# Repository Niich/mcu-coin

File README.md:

# mcu-coin
## Design Goals
- make a device that is similare in form factor to military challange coins
- production cost needs to be in the range of traditional coins ($5-$15)

## V1.0 features
- based on ESP32C3
- 100mAh 302020 battery
- 7 addressable RGBs
- 2 GPIO buttons
- hardware power on/off and boot select **
    - to reduce power draw when off and to guard against bad firmare bricking the device since once it is assembled, battery soldered in and parts glued together, removing power to reset device would be very difficult.
- USB charging
- wireless charging ***
- WiFi ***
- bluetooth ***

** not working on original design but manual fix found

*** Currently not working

## v1.0 known issues
- ✅ SW2 boot select button/GPIO9 
    - **Expected:** when held during boot ESP enters flashing mode.
    - **Observed:** device does not enter boot mode when button is held during boot.
    - **Fix:** After reviewing the ESP docs and the schematic issue was found to be that the button was connected to 3.3v instead of ground. Fixed by cutting trace to +3.3 and bridging the pin to the ground plane.

- ✅ SW1 on-off/GPIO6 
    - **Expected:** when device is off pressing this button should turn on the device. while device is active quick presses should be detected on GPIO6. Long pressing when "on" should turn off the device. 
    - **Observed:** Button does not turn the device on. but once on the press can be detected on GPIO6 and long press does turn the device off.
    - **Fix:** After reviewing the schematic issue was found to be that the button was connected to "MainPower" instead of +BATT. meaning that when the device is off there is no voltage on the switch so pressing it did nothing. Fix is connecting the button to +BATT and cutting trace to "MainPower"
    
- ❌ Wireless charging
    - **Expected:** when device placed on wireless charging pad it charges
    - **Observed:** Pad detects device but power delivery never stabalises it seems to be failing the negotiation. Issue has been observed on two differant wireless power transmitters
    - **Fix:** NONE. This is due to poor efficiency. If placed just right, wireless charging will work, but devices get VERY hot. To resolve this, the coil needs to be measured and revised in future designs. Additionally, the QI standard specifies a ferite layer behind the coil, which is not possible with the current placement of the coil.
- ❌ 2.4Ghz wireless (WifI/bluetooth)
    - **Expected:** device connects to WiFi.
    - **Observed:** When 2.4Ghz functions are enabled in firmware the device crashes. 
    - **Fix:** NONE. This is related to the luckup/crashing. When WiFi is activated, it interferes with the main clock and causes the device to lockup/crash.
- ❌ Crashing and hard locks
    - **Expected:** Device runs coninualy until turned of or battery is drained.
    - **Observed:** The device runs for a while but randomly locks up and requires a restart. The issue seems worse when LEDs are at full power.
    - **Fix:** NONE: This is caused by bad placement and routing of the main clock signal. Due to poor design, there is interferance and cross-talk that degrade the clock signal and cause CPU lockup.
- [ ] Acrylic spacer and diffuser
    - **Expected:** Top and bottom PCB are seperated and atteched to a 3mm acrylic spacer.
    - **Observed:** Although the 302020 battery is listed as 3mm thick it is actualy slightly larger so the acrylic part is not thick enought to connect both sides without bending and placing pressure on the LiPo battery
    - **Ideas:** Make a thicker spacer. 1/8" might be ehough since that is 3.17mm

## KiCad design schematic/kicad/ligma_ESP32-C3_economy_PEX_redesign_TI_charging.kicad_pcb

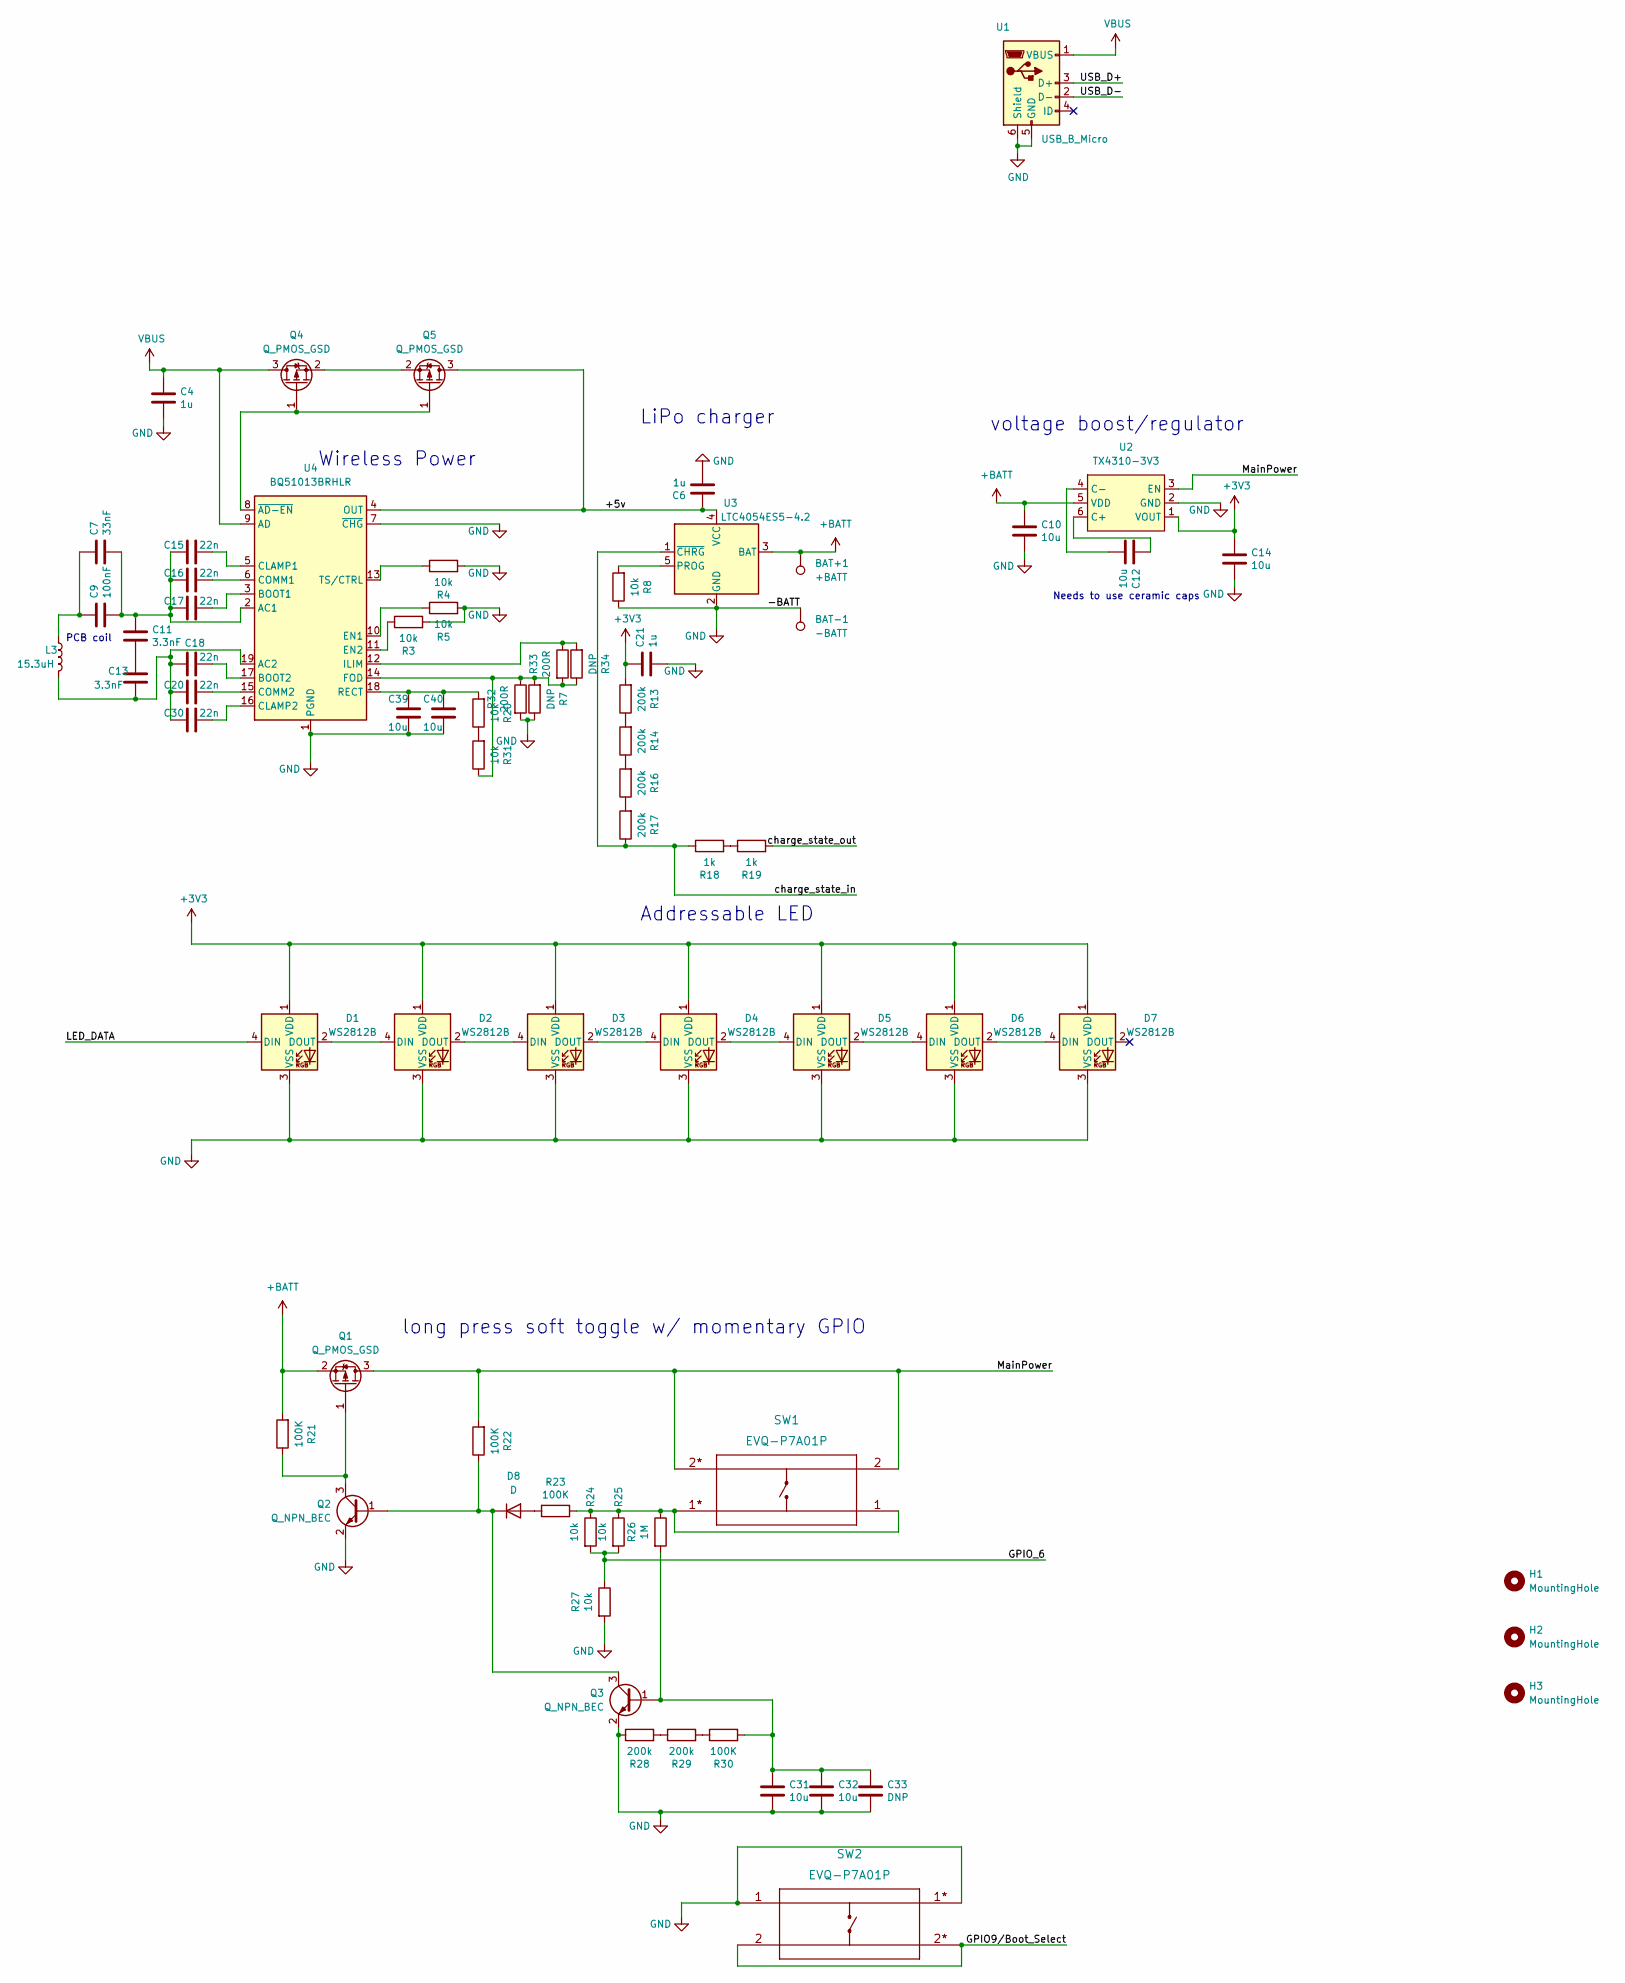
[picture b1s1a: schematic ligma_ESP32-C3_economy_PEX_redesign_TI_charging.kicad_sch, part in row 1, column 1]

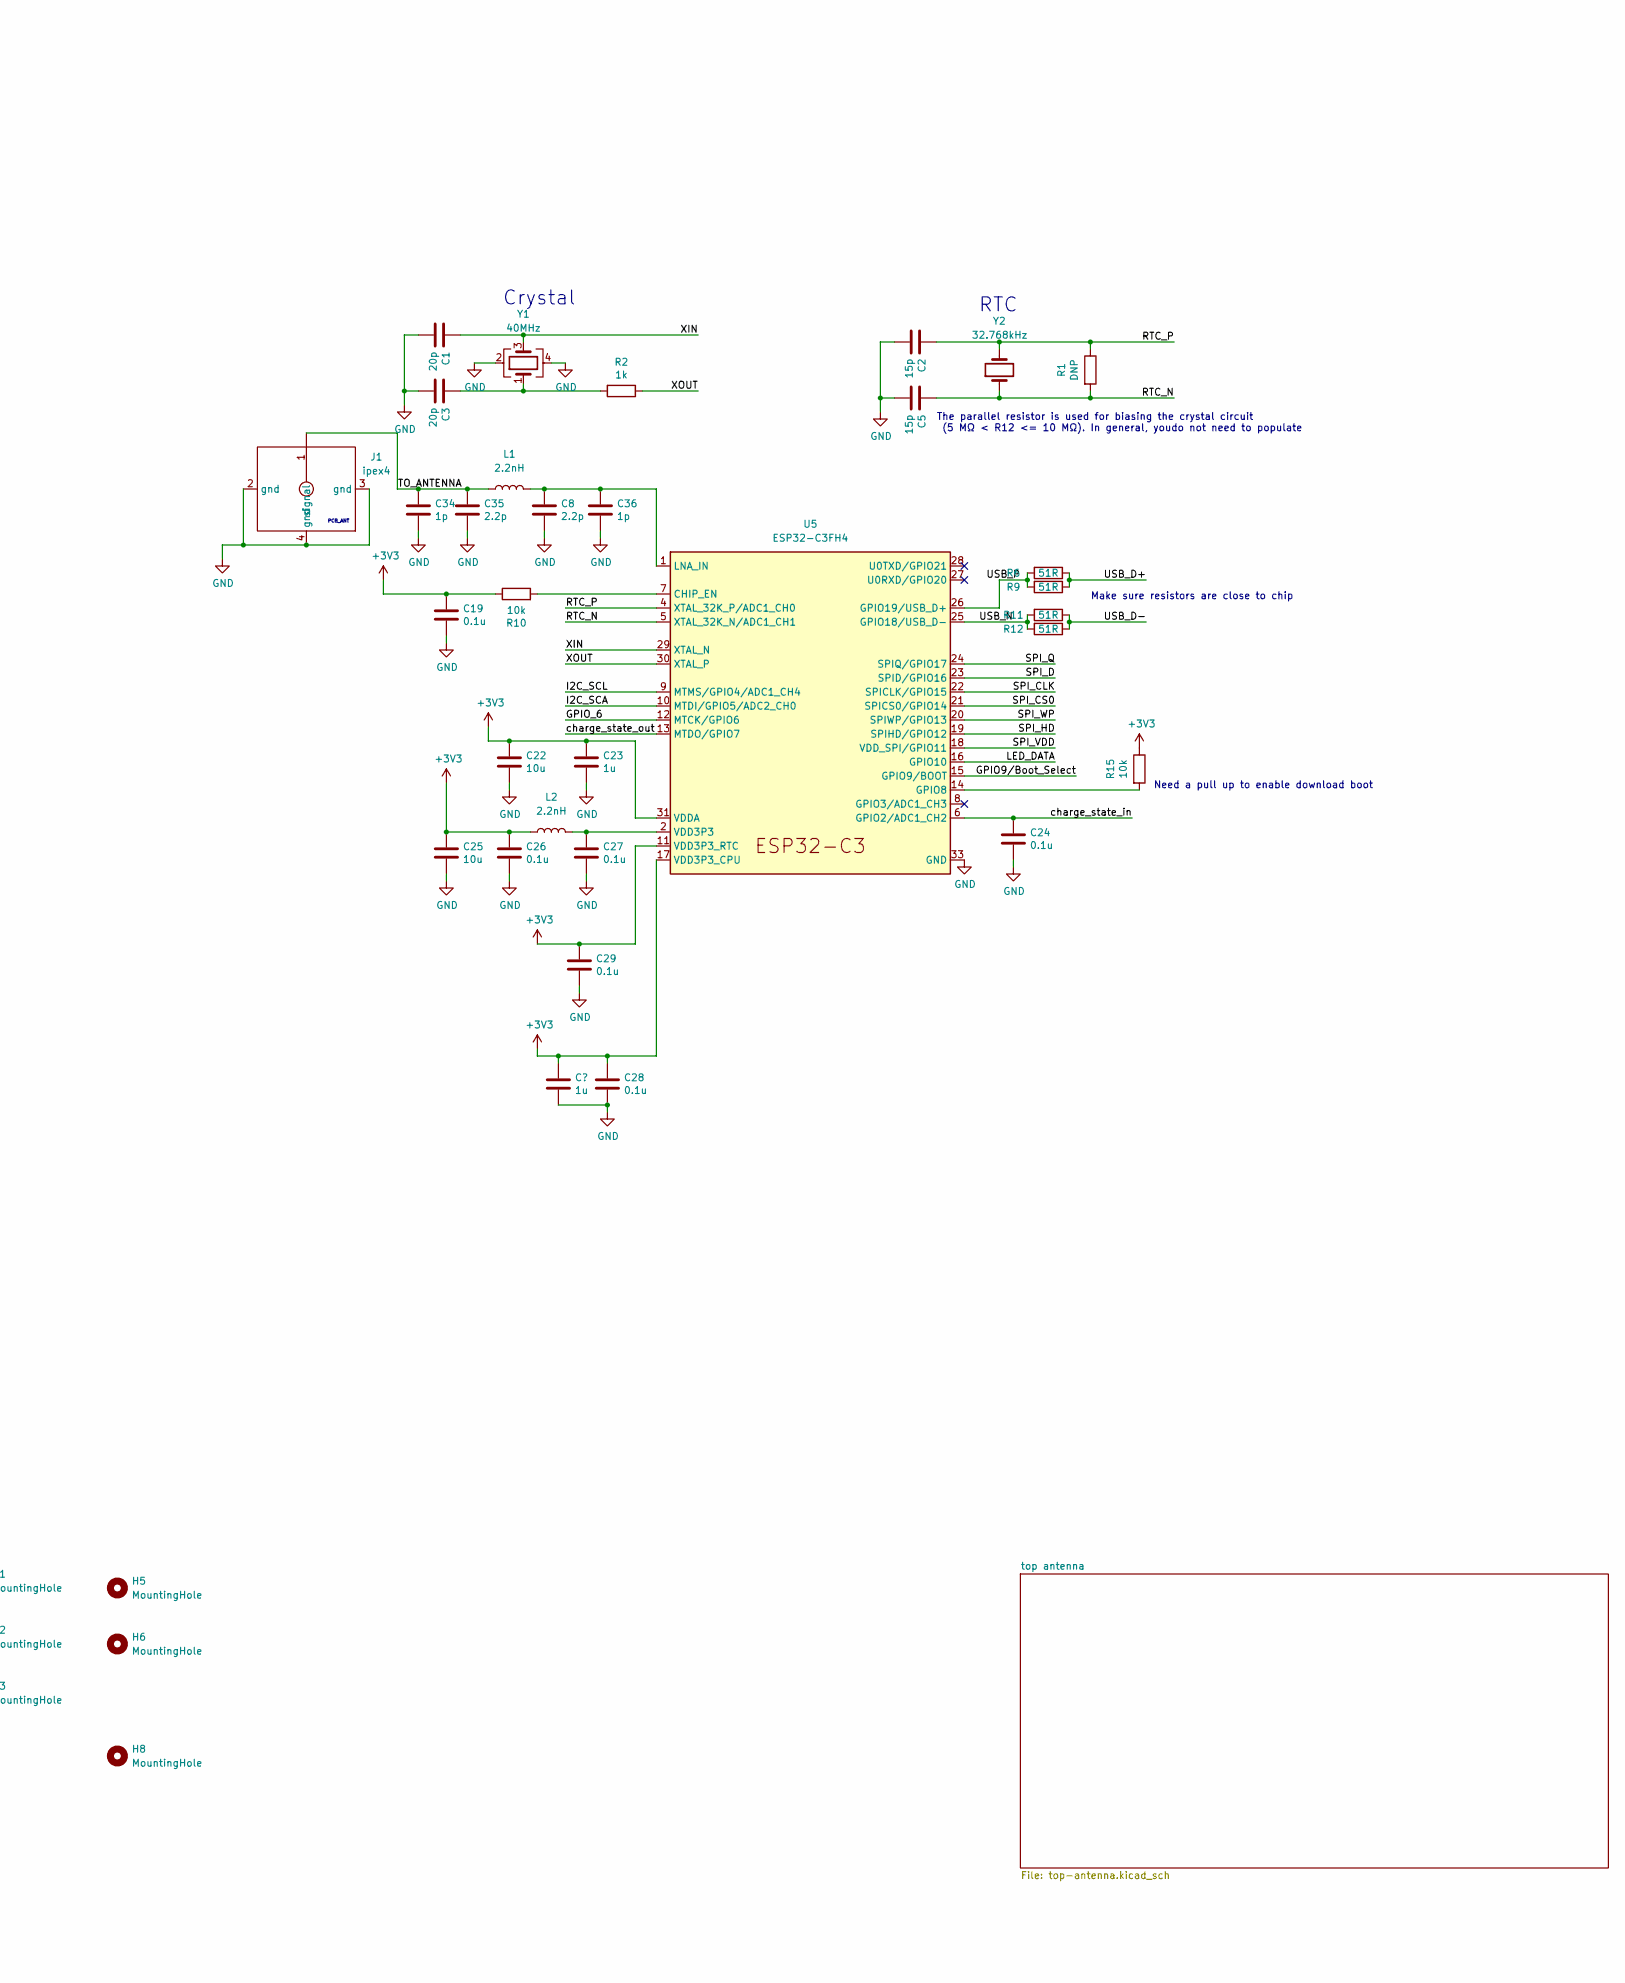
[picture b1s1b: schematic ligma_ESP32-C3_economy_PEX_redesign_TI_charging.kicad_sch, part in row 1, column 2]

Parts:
BAT+1: +BATT; TestPoint_Pad_2.0x2.0mm
BAT-1: -BATT; TestPoint_Pad_2.0x2.0mm
C1, C3: 20p; C_0402_1005Metric; MFR.Part # 0402CG200J500NT; LCSC Part # C1554
C2, C5: 15p; C_0402_1005Metric; MFR.Part # 0402CG150J500NT; LCSC Part # C1548
C4, C6, C21, C23: 1u; C_0402_1005Metric; MFR.Part # CL05A105KA5NQNC; LCSC Part # C52923
C7: 33nF; C_0402_1005Metric; MFR.Part # C1585; LCSC Part # C1585
C8, C35: 2.2p; C_0402_1005Metric; MFR.Part # 0402CG2R2C500NT; LCSC Part # C1559
C9: 100nF; C_0402_1005Metric; MFR.Part # CL05B104KB54PNC; LCSC Part # C307331
C10, C12, C14, C22, C25, C31, C32, C39, C40: 10u; C_0402_1005Metric; MFR.Part # CL05A106MQ5NUNC; LCSC Part # C15525
C11, C13: 3.3nF; C_0402_1005Metric; MFR.Part # CL05B332KB5NNNC; LCSC Part # C26404
C15, C16, C17, C18, C20, C30: 22n; C_0402_1005Metric; MFR.Part # 0402B223K500NT; LCSC Part # C1532
C19, C24, C26, C27, C28, C29: 0.1u; C_0402_1005Metric; MFR.Part # CL05B104KB54PNC; LCSC Part # C307331
C33: DNP; C_0402_1005Metric
C34, C36: 1p; C_0402_1005Metric; MFR.Part # 0402CG1R0C500NT; LCSC Part # C1550
D1, D2, D3, D4, D5, D6, D7: WS2812B; LED_WS2812B_PLCC4_5.0x5.0mm_P3.2mm; MFR.Part # WS2812E-V5; LCSC Part # C2920042
D8: D; SOD_123; MFR.Part # B5819W SL; LCSC Part # C8598
H1, H2, H3, H5, H6, H8: MountingHole; coin-mouse-bite
J1: ipex4; HC-RF-IPEX2020-04; MFR.Part # HC-RF-IPEX2020-04; LCSC Part # C2894921
L1, L2: 2.2nH; L_0402_1005Metric; MFR.Part # CLH1005T-2N2S-S; LCSC Part # C108254
L3: 15.3uH; 15.3uH-coil
Q1, Q4, Q5: Q_PMOS_GSD; SOT-23; MFR.Part # SI2301CDS-T1-GE3; LCSC Part # C10487
Q2, Q3: Q_NPN_BEC; SOT-23; MFR.Part # FHS3904-ME; LCSC Part # C336147
R1, R7, R34: DNP; R_0402_1005Metric
R2, R18, R19: 1k; R_0402_1005Metric; MFR.Part # 0402WGF1001TCE; LCSC Part # C11702
R3, R4, R5: 10k; R_0402_1005Metric; MFR.Part # 0402WGF1000TCE; LCSC Part # C25744
R6, R9, R11, R12: 51R; R_0402_1005Metric; MFR.Part # 0402WGF5100TCE; LCSC Part # C25123
R8, R10, R15, R20, R24, R25, R27, R31: 10k; R_0402_1005Metric; MFR.Part # 0402WGF1002TCE; LCSC Part # C25744
R13, R14, R16, R17, R28, R29: 200k; R_0402_1005Metric; MFR.Part # 0402WGF2003TCE; LCSC Part # C25764
R21, R22, R23, R30: 100K; R_0402_1005Metric; MFR.Part # 0402WGF1003TCE; LCSC Part # C25741
R26: 1M; R_0402_1005Metric; MFR.Part # 0402WGF1004TCE; LCSC Part # C26083
R32, R33: 200R; R_0402_1005Metric; MFR.Part # 0402WGF2000TCE; LCSC Part # C25087
SW1, SW2: EVQ-P7A01P; MFR.Part # EVQP7A01P; LCSC Part # C79167
U1: USB_B_Micro; USB-Micro-B-BTC-MC5S-42; MFR.Part # BTC-MC5S-42; LCSC Part # C2908213
U2: TX4310-3V3; SOT-23-6; MFR.Part # TX4310B; LCSC Part # C448640
U3: LTC4054ES5-4.2; TSOT-23-5; MFR.Part # TP4054-42-SOT25R; LCSC Part # C32574
U4: BQ51013BRHLR; Texas_VQFN-RHL-20; MFR.Part # BQ51013BRHLR; LCSC Part # C55663
U5: ESP32-C3FH4; QFN-32-1EP_5x5mm_P0.5mm_EP3.45x3.45mm; MFR.Part # ESP32-C3FH4; LCSC Part # C2858491
Y1: 40MHz; Crystal_SMD_3225-4Pin_3.2x2.5mm; MFR.Part # 3S40000131; LCSC Part # C516573
Y2: 32.768kHz; Crystal_SMD_3215-2Pin_3.2x1.5mm; MFR.Part # Q13FC1350000400; LCSC Part # C32346

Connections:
+BATT: BAT+1.1, C10.1, Q1.2 (S), R21.2, U2.5 (VDD), U3.3 (BAT)
/+5v: C6.1, Q5.3 (D), U3.4 (VCC), U4.4 (OUT)
/GPIO9/Boot_Select: SW2.2, SW2.2*, U5.15 (GPIO9/BOOT)
/GPIO_6: R24.2, R25.2, R27.1, U5.12 (MTCK/GPIO6)
/I2C_SCA: U5.10 (MTDI/GPIO5/ADC2_CH0)
/I2C_SCL: U5.9 (MTMS/GPIO4/ADC1_CH4)
/LED_DATA: D1.4 (DIN), U5.16 (GPIO10)
/MainPower: Q1.3 (D), R22.2, SW1.2, SW1.2*, U2.3 (EN)
/RTC_N: C5.1, R1.2, U5.5 (XTAL_32K_N/ADC1_CH1), Y2.1
/RTC_P: C2.1, R1.1, U5.4 (XTAL_32K_P/ADC1_CH0), Y2.2
/SPI_CLK: U5.22 (SPICLK/GPIO15)
/SPI_CS0: U5.21 (SPICS0/GPIO14)
/SPI_D: U5.23 (SPID/GPIO16)
/SPI_HD: U5.19 (SPIHD/GPIO12)
/SPI_Q: U5.24 (SPIQ/GPIO17)
/SPI_VDD: U5.18 (VDD_SPI/GPIO11)
/SPI_WP: U5.20 (SPIWP/GPIO13)
/TO_ANTENNA: C34.1, C35.1, J1.1 (signal), L1.1
/USB_D+: R6.1, R9.1, U1.3 (D+)
/USB_D-: R11.1, R12.1, U1.2 (D-)
/USB_N: R11.2, R12.2, U5.25 (GPIO18/USB_D-)
/USB_P: R6.2, R9.2, U5.26 (GPIO19/USB_D+)
/XIN: C1.1, U5.29 (XTAL_N), Y1.3
/XOUT: R2.1, U5.30 (XTAL_P)
/charge_state_in: C24.1, R17.1, R18.1, U3.1 (~CHRG), U5.6 (GPIO2/ADC1_CH2)
/charge_state_out: R19.2, U5.13 (MTDO/GPIO7)
GND: BAT-1.1, C1.2, C2.2, C3.2, C4.2, C5.2, C6.2, C8.2, C10.2, C14.2, C19.2, C21.2, C22.2, C23.2, C24.2, C25.2, C26.2, C27.2, C28.2, C29.2, C31.2, C32.2, C33.2, C34.2, C35.2, C36.2, C39.2, C40.2, D1.3 (VSS), D2.3 (VSS), D3.3 (VSS), D4.3 (VSS), D5.3 (VSS), D6.3 (VSS), D7.3 (VSS), J1.2 (gnd), J1.3 (gnd), J1.4 (gnd), Q2.2 (E), Q3.2 (E), R3.2, R4.2, R5.2, R7.1, R8.1, R27.2, R28.1, R32.2, U1.5 (GND), U1.6 (Shield), U2.2 (GND), U3.2 (GND), U4.1 (PGND), U4.7 (~CHG), U4.20 (PGND), U4.21 (PGND), U5.33 (GND), Y1.2, Y1.4
unnamed: C3.1, R2.2, Y1.1
unnamed: C7.1, C9.1, L3.1
unnamed: C7.2, C9.2, C11.1, C15.1, C16.1, C17.1, U4.2 (AC1)
unnamed: C11.2, C13.1
unnamed: C12.1, U2.6 (C+)
unnamed: C12.2, U2.4 (C-)
unnamed: C13.2, C18.1, C20.1, C30.1, L3.2, U4.19 (AC2)
unnamed: C15.2, U4.5 (CLAMP1)
unnamed: C16.2, U4.6 (COMM1)
unnamed: C17.2, U4.3 (BOOT1)
unnamed: C18.2, U4.17 (BOOT2)
unnamed: C20.2, U4.15 (COMM2)
unnamed: C27.1, L2.2, U5.2 (VDD3P3), U5.3 (VDD3P3)
unnamed: C30.2, U4.16 (CLAMP2)
unnamed: C31.1, C32.1, C33.1, Q3.1 (B), R26.2, R30.2
unnamed: C8.1, C36.1, L1.2, U5.1 (LNA_IN)
unnamed: C39.1, C40.1, R20.2, U4.18 (RECT)
unnamed: D1.2 (DOUT), D2.4 (DIN)
unnamed: D2.2 (DOUT), D3.4 (DIN)
unnamed: D3.2 (DOUT), D4.4 (DIN)
unnamed: D4.2 (DOUT), D5.4 (DIN)
unnamed: D5.2 (DOUT), D6.4 (DIN)
unnamed: D6.2 (DOUT), D7.4 (DIN)
unnamed: D8.1 (K), Q2.1 (B), Q3.3 (C), R22.1
unnamed: D8.2 (A), R23.2
unnamed: Q1.1 (G), Q2.3 (C), R21.1
unnamed: Q4.1 (G), Q5.1 (G), U4.8 (~AD-EN)
unnamed: Q4.2 (S), Q5.2 (S)
unnamed: R3.1, U4.11 (EN2)
unnamed: R4.1, U4.13 (TS/CTRL)
unnamed: R5.1, U4.10 (EN1)
unnamed: R7.2, R31.1, R32.1, R33.2, R34.1, U4.14 (FOD)
unnamed: R8.2, U3.5 (PROG)
unnamed: R10.2, U5.7 (CHIP_EN)
unnamed: R13.1, R14.2
unnamed: R14.1, R16.2
unnamed: R15.2, U5.14 (GPIO8)
unnamed: R16.1, R17.2
unnamed: R18.2, R19.1
unnamed: R20.1, R31.2
unnamed: R23.1, R24.1, R25.1, R26.1, SW1.1, SW1.1*
unnamed: R28.2, R29.1
unnamed: R29.2, R30.1
unnamed: R33.1, R34.2, U4.12 (ILIM)
VBUS: C4.1, Q4.3 (D), U1.1 (VBUS), U4.9 (AD)

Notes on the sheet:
LiPo charger
PCB_ANT
voltage boost/regulator
Crystal
Needs to use ceramic caps
Wireless Power
PCB coil
Need a pull up to enable download boot
RTC
The parallel resistor is used for biasing the crystal circuit (5 MΩ < R12 <= 10 MΩ). In general, youdo not need to populate
long press soft toggle w/ momentary GPIO
Make sure resistors are close to chip
Addressable LED

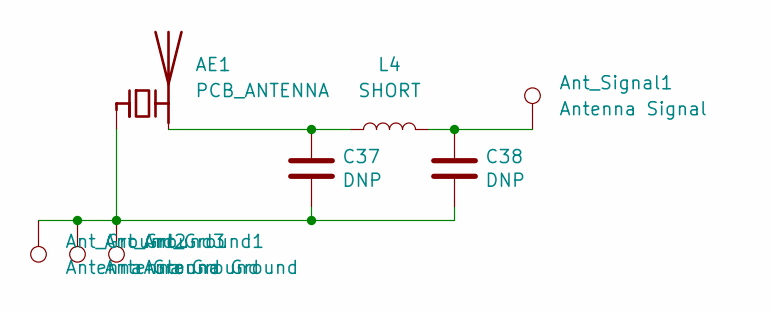
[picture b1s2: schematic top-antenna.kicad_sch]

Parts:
AE1: PCB_ANTENNA; 2.4_Ti
Ant_Ground1, Ant_Ground2, Ant_Ground3: Antenna Ground; SolderWirePad_1x01_SMD_1x2mm
Ant_Signal1: Antenna Signal; SolderWirePad_1x01_SMD_1x2mm
C37, C38: DNP; C_0402_1005Metric
L4: SHORT; L_0402_1005Metric; LCSC Part # C17168

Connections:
unnamed: AE1.1 (FEED), Ant_Ground1.1, Ant_Ground2.1, Ant_Ground3.1, C37.2, C38.2
unnamed: AE1.2 (PCB_Trace), C37.1, L4.1
unnamed: Ant_Signal1.1, C38.1, L4.2

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
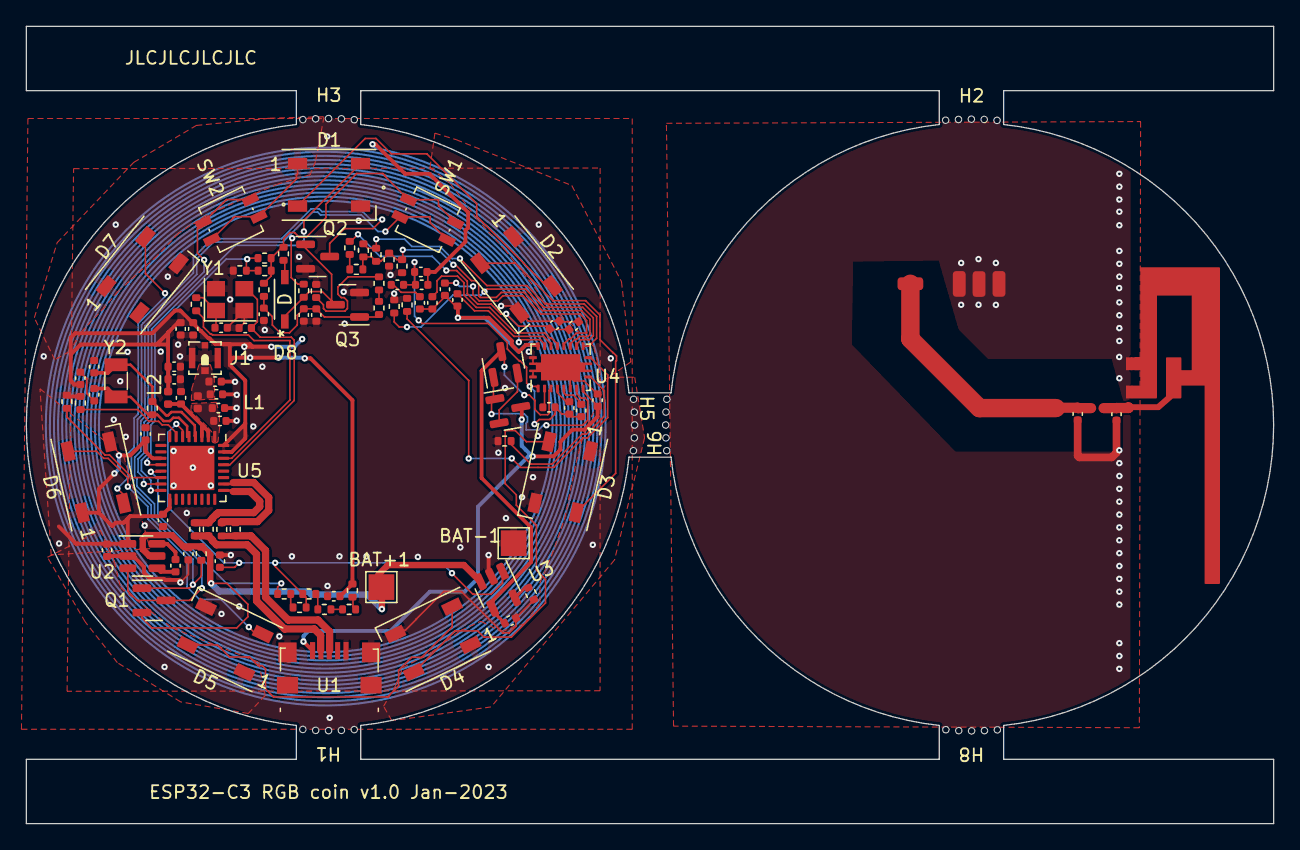
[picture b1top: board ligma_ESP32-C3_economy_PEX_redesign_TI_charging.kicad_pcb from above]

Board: 2 copper layers, 97.0 x 62.0 mm, 114 parts (1 on the bottom side), 67 nets.

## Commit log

2023-03-26 add pcb kicad files and first docs img
2023-03-26 add project images
2023-03-26 mark PowerSwitch issues as fixed
2023-03-26 add issue about battery and spacer not working together
2024-02-23 Update README.md
    added new info regarding the issues and fixes.
2024-02-24 Create example-arduino.ino
    add example arduino firmware file that cycles through some color modes.

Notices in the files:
parts and their libraries:
Copyright 2021 Accelerated Designs. All rights reserved.
